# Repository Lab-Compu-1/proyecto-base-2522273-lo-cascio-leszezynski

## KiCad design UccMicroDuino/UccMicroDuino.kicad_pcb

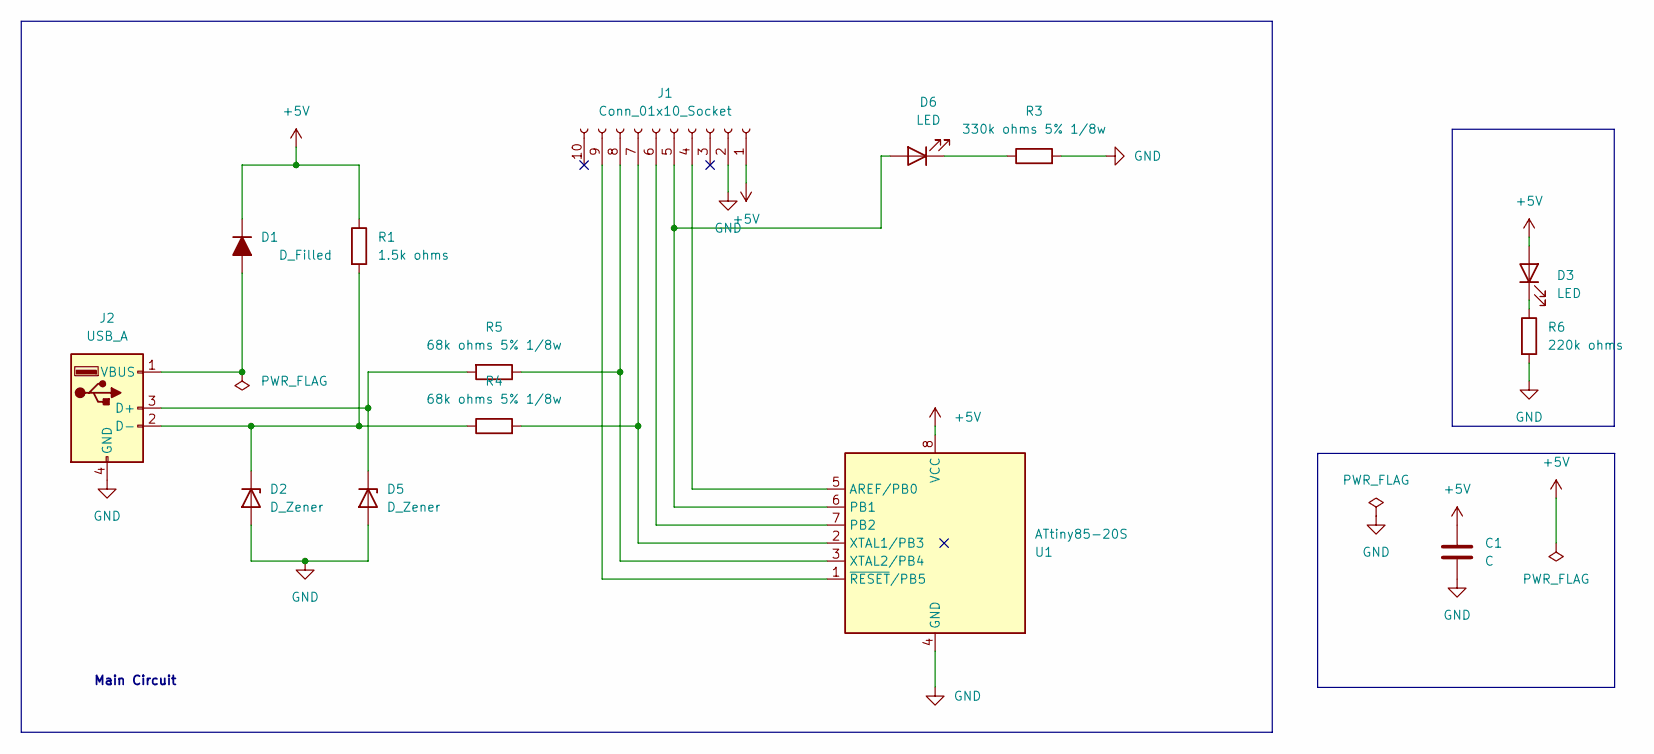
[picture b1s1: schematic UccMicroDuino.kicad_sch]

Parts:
C1: C; C_0805_2012Metric_Pad1.18x1.45mm_HandSolder
D1: D_Filled; D_MiniMELF
D2, D5: D_Zener; D_SOD-123
D3, D6: LED; ledSMD
J1: Conn_01x10_Socket; PinHeader_1x10_P2.54mm_Vertical
J2: USB_A; USB_A_UCC
R1: 1.5k ohms; R_0805_2012Metric_Pad1.20x1.40mm_HandSolder
R3: 330k ohms 5% 1/8w; R_0805_2012Metric_Pad1.20x1.40mm_HandSolder
R4, R5: 68k ohms 5% 1/8w; R_0805_2012Metric_Pad1.20x1.40mm_HandSolder
R6: 220k ohms; R_0805_2012Metric_Pad1.20x1.40mm_HandSolder
U1: ATtiny85-20S; SOIC-8W_5.3x5.3mm_P1.27mm

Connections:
+5V: C1.1, D1.1 (K), D3.2 (A), J1.1, R1.1, U1.8 (VCC)
GND: C1.2, D2.2 (A), D5.2 (A), J1.2, J2.4 (GND), R3.2, R6.2, U1.4 (GND)
unnamed: D1.2 (A), J2.1 (VBUS)
unnamed: D2.1 (K), J2.2 (D-), R1.2, R4.1
unnamed: D3.1 (K), R6.1
unnamed: D5.1 (K), J2.3 (D+), R5.2
unnamed: D6.2 (A), J1.5, U1.6 (PB1)
unnamed: D6.1 (K), R3.1
unnamed: J1.4, U1.5 (AREF/PB0)
unnamed: J1.6, U1.7 (PB2)
unnamed: J1.7, R4.2, U1.2 (XTAL1/PB3)
unnamed: J1.8, R5.1, U1.3 (XTAL2/PB4)
unnamed: J1.9, U1.1 (~RESET/PB5)

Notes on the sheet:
Main Circuit

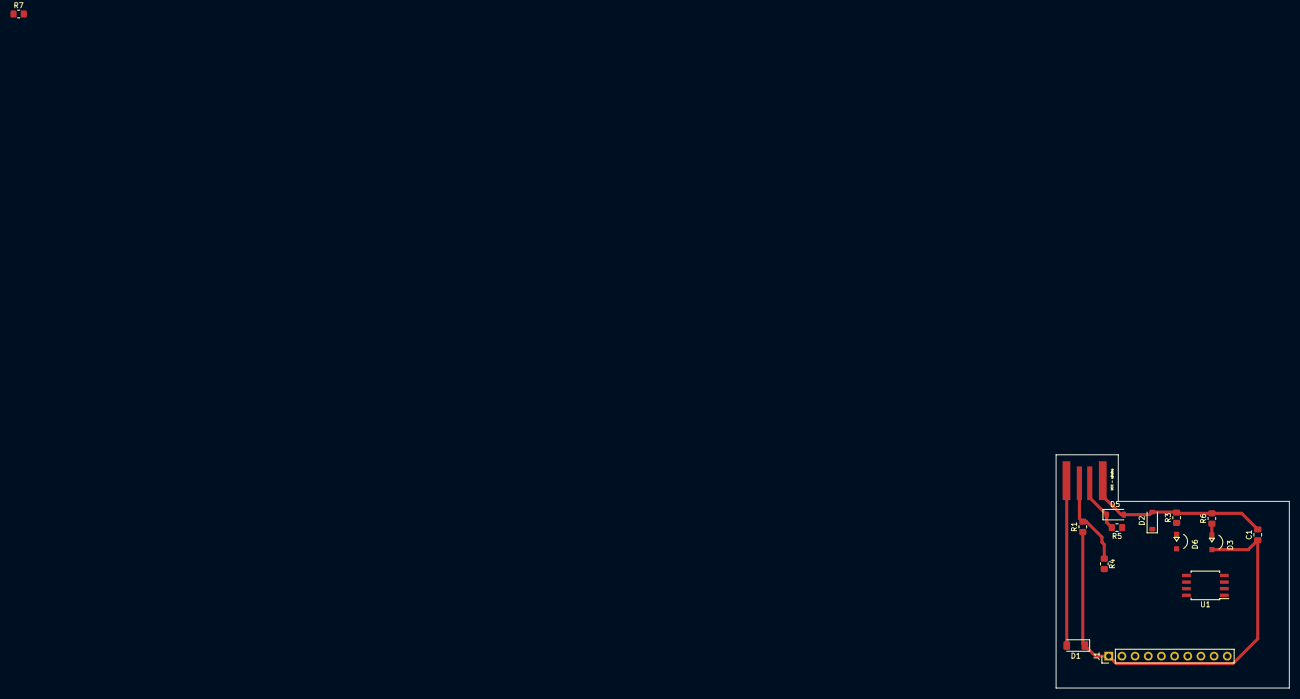
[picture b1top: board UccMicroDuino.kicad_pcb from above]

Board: 2 copper layers, 45.0 x 45.0 mm, 15 parts (0 on the bottom side), 13 nets.

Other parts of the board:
R7: R_Small; R_0805_2012Metric_Pad1.20x1.40mm_HandSolder

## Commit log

2025-05-23 GitHub Classroom Feedback
2025-05-23 Setting up GitHub Classroom Feedback
2025-05-23 proyecto terminado
